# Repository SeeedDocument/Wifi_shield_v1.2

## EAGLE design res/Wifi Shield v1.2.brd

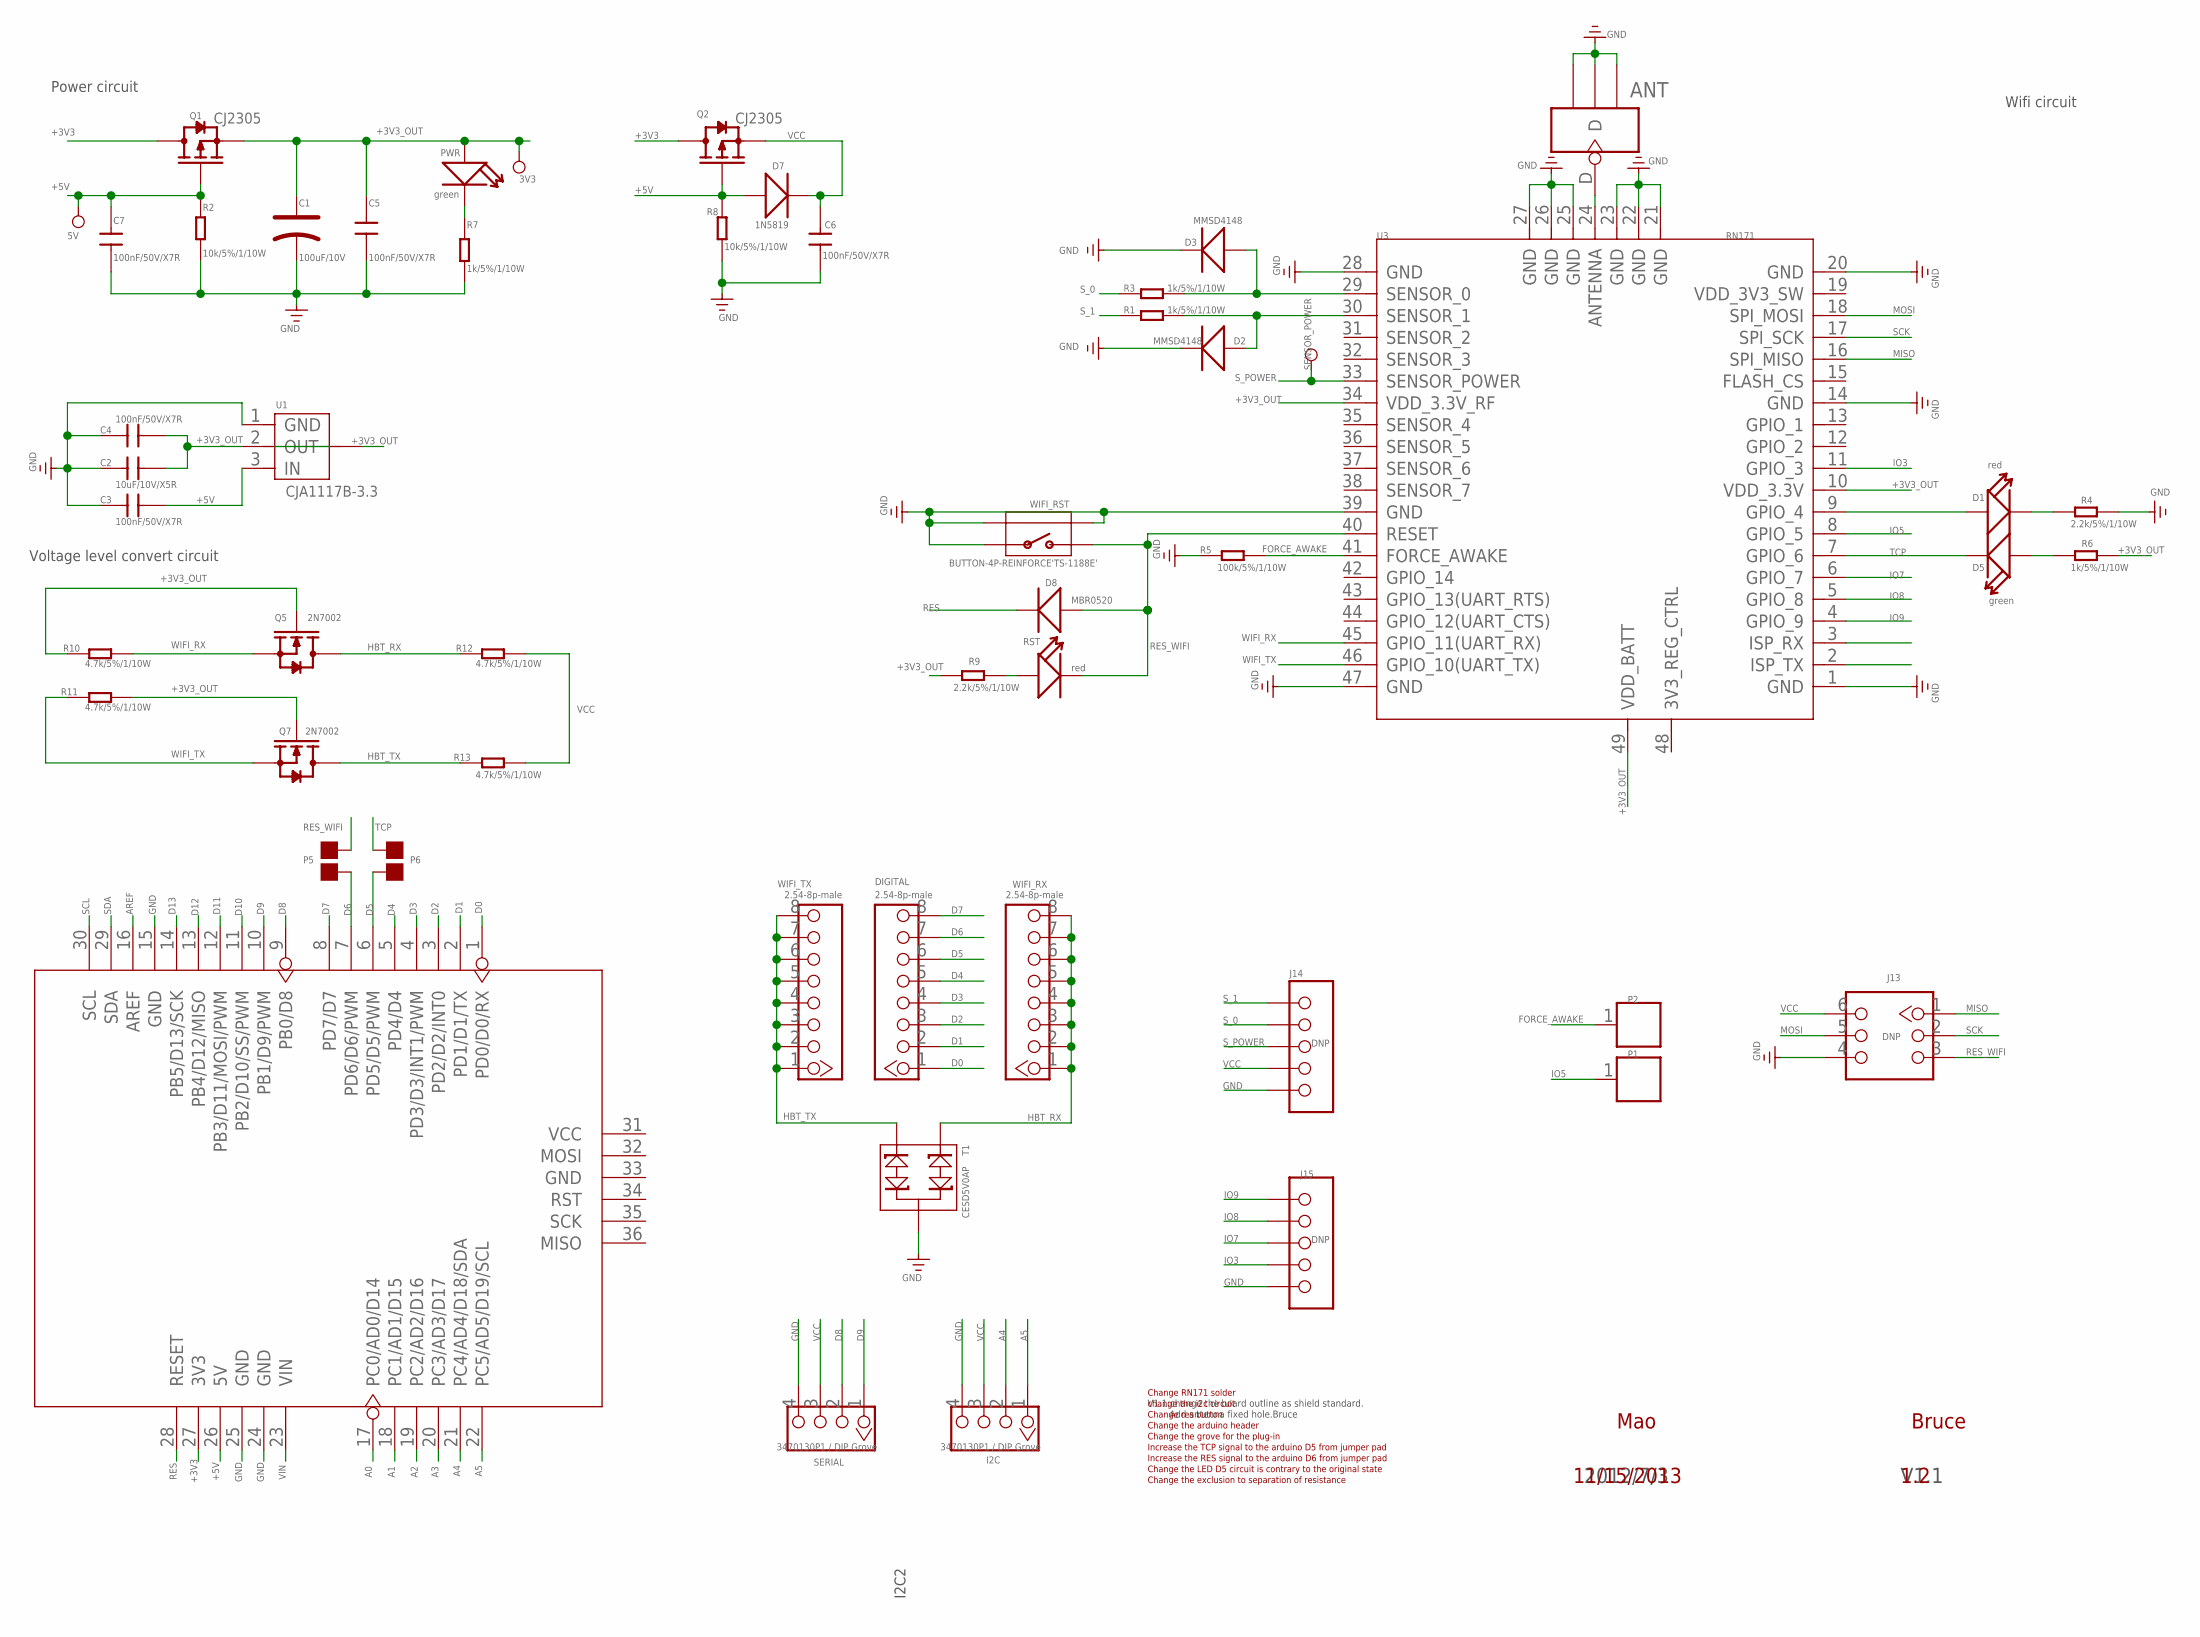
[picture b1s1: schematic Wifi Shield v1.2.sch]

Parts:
3V3, 5V: PAD-TEST-POINT-CIRCLE_SIZE_3030; TP_3535
ANT1: ANT; 4P-U-FL
C1: 100uF/10V; AVX-B
C2: 10uF/10V/X5R; 0603
C3, C4, C5, C6, C7: 100nF/50V/X7R; 0603
D1: red; LED-0603
D2, D3: MMSD4148; SOD123-2.7X1.6
D5: green; LED-0603
D7: 1N5819; D2010
D8: MBR0520; SOD123-2.7X1.6
DIGITAL: 2.54-8p-male; 8P-2.54
I2C: 3470130P1 / DIP Grove; 4P-2.0
J13: DNP; 2X3P-2.54
J14, J15: DNP; 5P-2.54
P1, P2: DNP; 1P-65/35MIL
P5, P6: DNP; 2P-SMD-1.78X1.27
PWR: green; LED-0603
Q1, Q2: CJ2305; SOT23
Q5, Q7: 2N7002; SOT23
R1, R3, R6, R7: 1k/5%/1/10W; 0603
R2, R8: 10k/5%/1/10W; 0603
R4, R9: 2.2k/5%/1/10W; 0603
R5: 100k/5%/1/10W; 0603
R10, R11, R12, R13: 4.7k/5%/1/10W; 0603
RST: red; LED-0603
SENSOR_POWER: PAD-TEST-POINT-CIRCLE_SIZE_3030; TP_3535
SERIAL: 3470130P1 / DIP Grove; 4P-2.0
T1: CESD5V0AP; SOT23
U1: CJA1117B-3.3; SOT89
U2: ARDUINO'W/O-SILK'; ARDUINO-W/O-SILK
U3: RN171; 49P-1.27-26.67X17.78
WIFI_RST: BUTTON-4P-REINFORCE'TS-1188E'; 4P-SMD-7X3.5X3.5H
WIFI_RX: 2.54-8p-male; 8P-2.54
WIFI_TX: 2.54-8p-male; 8P-2.54

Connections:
+3V3: Q1.3 (D), Q2.3 (D), U2.27 (3V3)
+3V3_OUT: 3V3.T, C1.+, C2.2, C4.2, C5.1, PWR.+, Q1.2 (S), Q5.1 (G), Q7.1 (G), R6.1, R9.2, R10.2, R11.1, U1.2 (OUT), U1.4 (TAB), U3.10 (VDD_3.3V), U3.34 (VDD_3.3V_RF), U3.49 (VDD_BATT)
+5V: 5V.T, C3.2, C7.1, D7.+, Q1.1 (G), Q2.1 (G), R2.1, R8.1, U1.3 (IN), U2.26 (5V)
A0: U2.17 (PC0/AD0/D14)
A1: U2.18 (PC1/AD1/D15)
A2: U2.19 (PC2/AD2/D16)
A3: U2.20 (PC3/AD3/D17)
A4: I2C.2, U2.21 (PC4/AD4/D18/SDA)
A5: I2C.1, U2.22 (PC5/AD5/D19/SCL)
AREF: U2.16 (AREF)
D0: DIGITAL.1, U2.1 (PD0/D0/RX)
D1: DIGITAL.2, U2.2 (PD1/D1/TX)
D2: DIGITAL.3, U2.3 (PD2/D2/INT0)
D3: DIGITAL.4, U2.4 (PD3/D3/INT1/PWM)
D4: DIGITAL.5, U2.5 (PD4/D4)
D5: DIGITAL.6, P6.2, U2.6 (PD5/D5/PWM)
D6: DIGITAL.7, P5.1, U2.7 (PD6/D6/PWM)
D7: DIGITAL.8, U2.8 (PD7/D7)
D8: SERIAL.2, U2.9 (PB0/D8)
D9: SERIAL.1, U2.10 (PB1/D9/PWM)
D10: U2.11 (PB2/D10/SS/PWM)
D11: U2.12 (PB3/D11/MOSI/PWM)
D12: U2.13 (PB4/D12/MISO)
D13: U2.14 (PB5/D13/SCK)
FORCE_AWAKE: P2.1, R5.1, U3.41 (FORCE_AWAKE)
GND: ANT1.GND1, ANT1.GND2, ANT1.GND3, C1.-, C2.1, C3.1, C4.1, C5.2, C6.2, C7.2, D2.1 (-), D3.1 (-), I2C.4, J13.4, J14.5, J15.5, R2.2, R4.1, R5.2, R7.1, R8.2, SERIAL.4, T1.3, U1.1 (GND), U2.15 (GND), U2.24 (GND), U2.25 (GND), U3.1 (GND), U3.14 (GND), U3.20 (GND), U3.21 (GND), U3.22 (GND), U3.23 (GND), U3.25 (GND), U3.26 (GND), U3.27 (GND), U3.28 (GND), U3.39 (GND), U3.47 (GND), WIFI_RST.1, WIFI_RST.S1, WIFI_RST.S2
HBT_RX: Q5.3 (D), R12.2, T1.1, WIFI_RX.1, WIFI_RX.2, WIFI_RX.3, WIFI_RX.4, WIFI_RX.5, WIFI_RX.6, WIFI_RX.7, WIFI_RX.8
HBT_TX: Q7.3 (D), R13.2, T1.2, WIFI_TX.1, WIFI_TX.2, WIFI_TX.3, WIFI_TX.4, WIFI_TX.5, WIFI_TX.6, WIFI_TX.7, WIFI_TX.8
IO3: J15.4, U3.11 (GPIO_3)
IO5: P1.1, U3.8 (GPIO_5)
IO7: J15.3, U3.6 (GPIO_7)
IO8: J15.2, U3.5 (GPIO_8)
IO9: J15.1, U3.4 (GPIO_9)
MISO: J13.1, U3.16 (SPI_MISO)
MOSI: J13.5, U3.18 (SPI_MOSI)
unnamed: R9.1, RST.+
unnamed: D3.2 (+), R3.1, U3.29 (SENSOR_0)
unnamed: D2.2 (+), R1.1, U3.30 (SENSOR_1)
unnamed: D5.+, R6.2
unnamed: ANT1.D, U3.24 (ANTENNA)
unnamed: D1.+, U3.9 (GPIO_4)
unnamed: D1.-, R4.2
unnamed: PWR.-, R7.2
RES: D8.1 (-), U2.28 (RESET)
RES_WIFI: D8.2 (+), J13.3, P5.2, RST.-, U3.40 (RESET), WIFI_RST.2
SCK: J13.2, U3.17 (SPI_SCK)
SCL: U2.30 (SCL)
SDA: U2.29 (SDA)
S_0: J14.2, R3.2
S_1: J14.1, R1.2
S_POWER: J14.3, SENSOR_POWER.T, U3.33 (SENSOR_POWER)
TCP: D5.-, P6.1, U3.7 (GPIO_6)
VCC: C6.1, D7.-, I2C.3, J13.6, J14.4, Q2.2 (S), R12.1, R13.1, SERIAL.3
VIN: U2.23 (VIN)
WIFI_RX: Q5.2 (S), R10.1, U3.45 (GPIO_11(UART_RX))
WIFI_TX: Q7.2 (S), R11.2, U3.46 (GPIO_10(UART_TX))

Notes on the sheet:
Power circuit
Wifi circuit
Voltage level convert circuit
V1.1
2012/7/3
V1.1:change the board outline as shield standard.
Add antenna fixed hole.Bruce
I2C2
Mao
change the i2c circuit
Change res button
Change the arduino header
Change RN171 solder
Change the grove for the plug-in
Increase the TCP signal to the arduino D5 from jumper pad
Increase the RES signal to the arduino D6 from jumper pad
Change the LED D5 circuit is contrary to the original state
Change the exclusion to separation of resistance
Bruce
1.2
11/15/2013

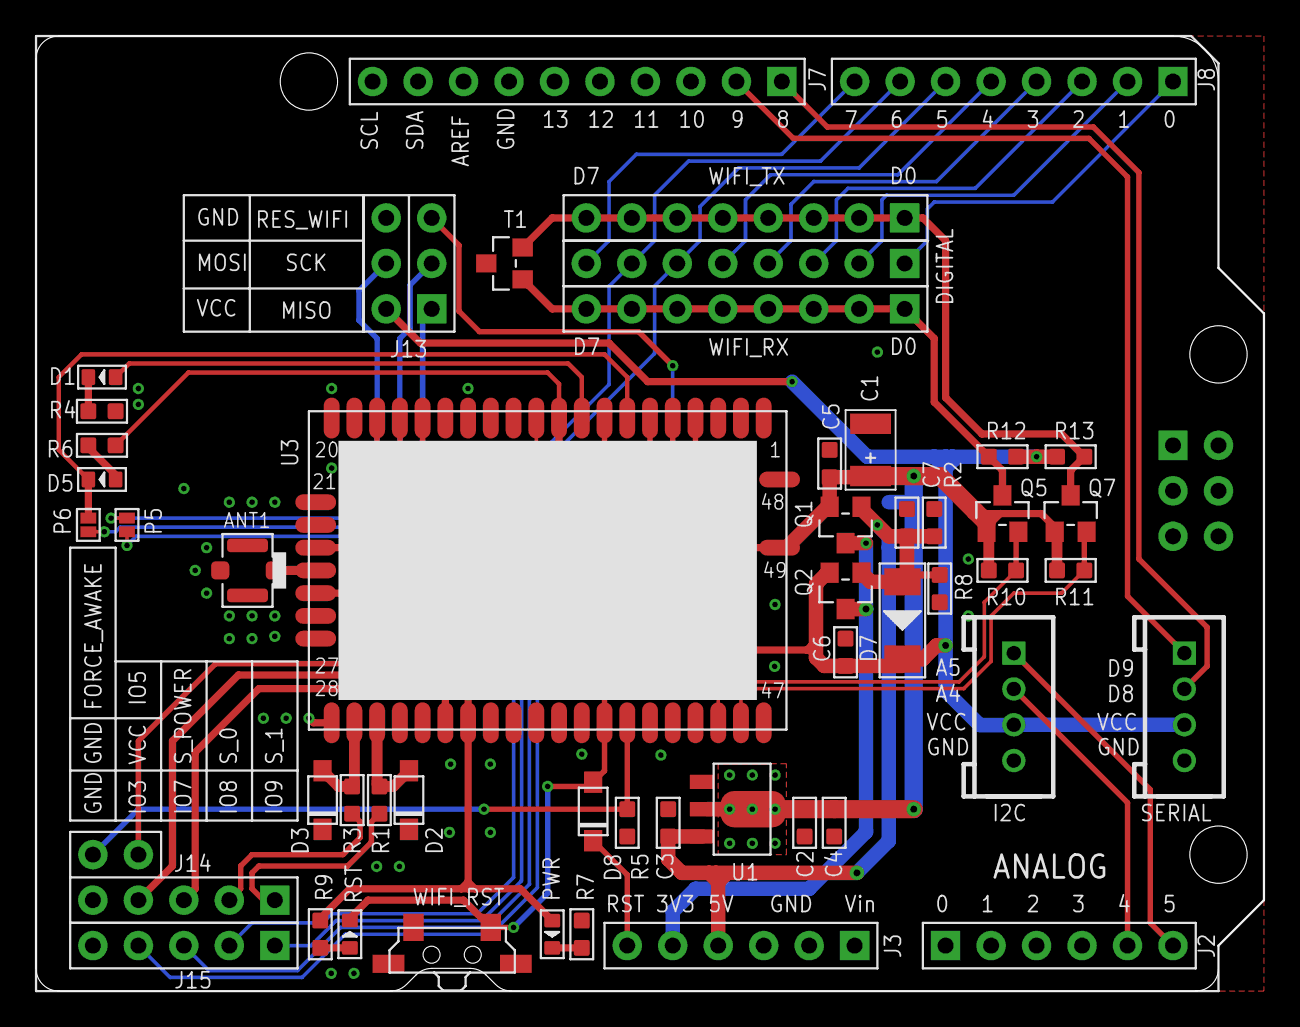
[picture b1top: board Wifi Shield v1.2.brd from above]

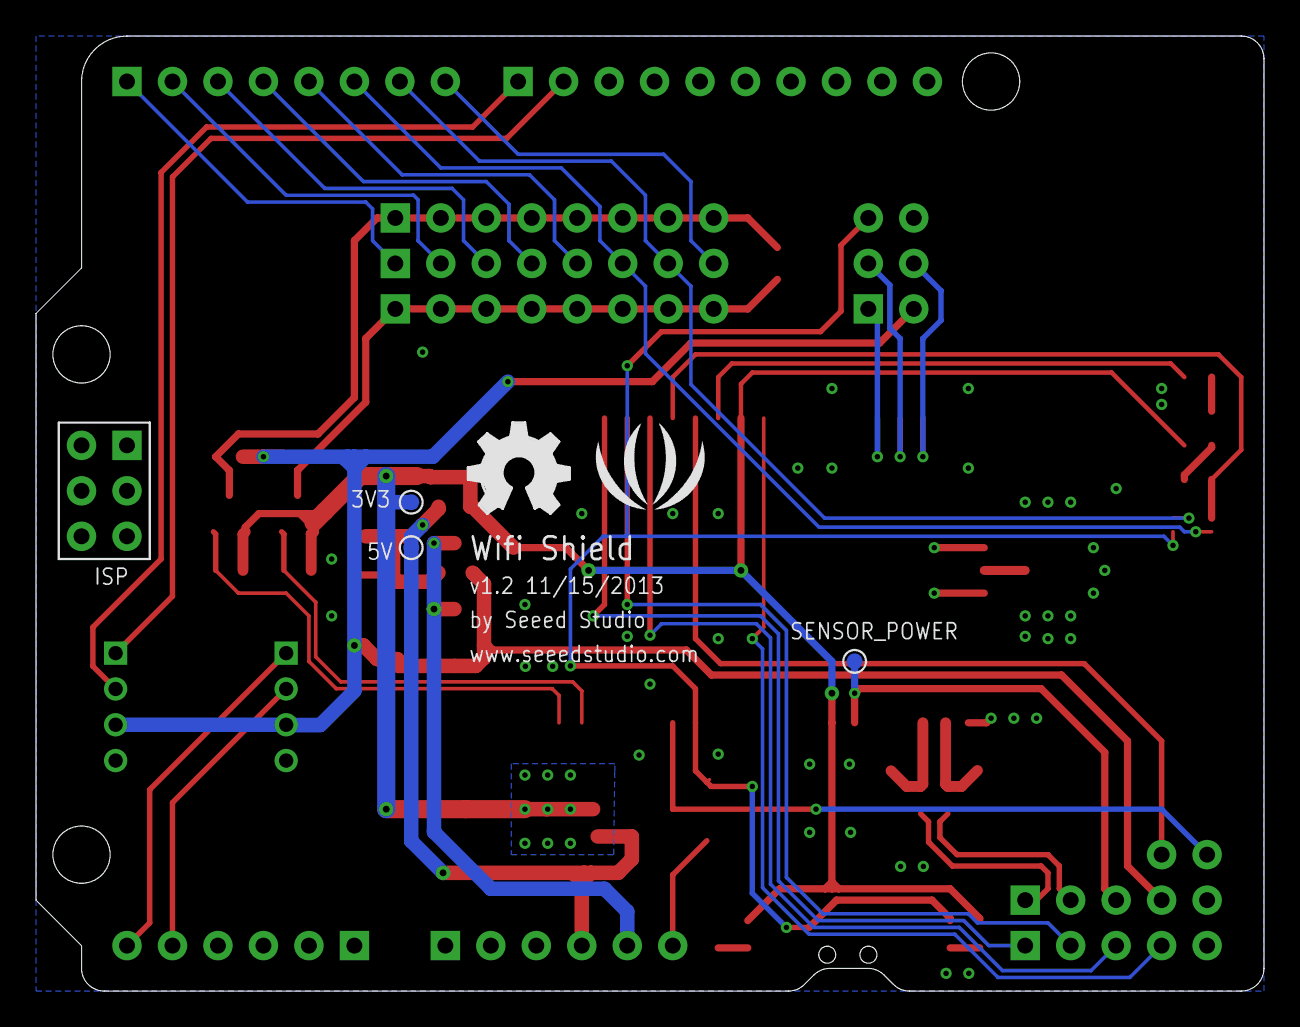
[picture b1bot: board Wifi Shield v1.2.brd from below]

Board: 2 copper layers, 68.6 x 53.3 mm, 55 parts (5 on the bottom side), 44 nets.

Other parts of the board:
U$1: OSHW_FILLX200_NOTEXT
U$2: LOGO_SILK

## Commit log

2017-06-04 upgrade
2019-11-06 add
    add
